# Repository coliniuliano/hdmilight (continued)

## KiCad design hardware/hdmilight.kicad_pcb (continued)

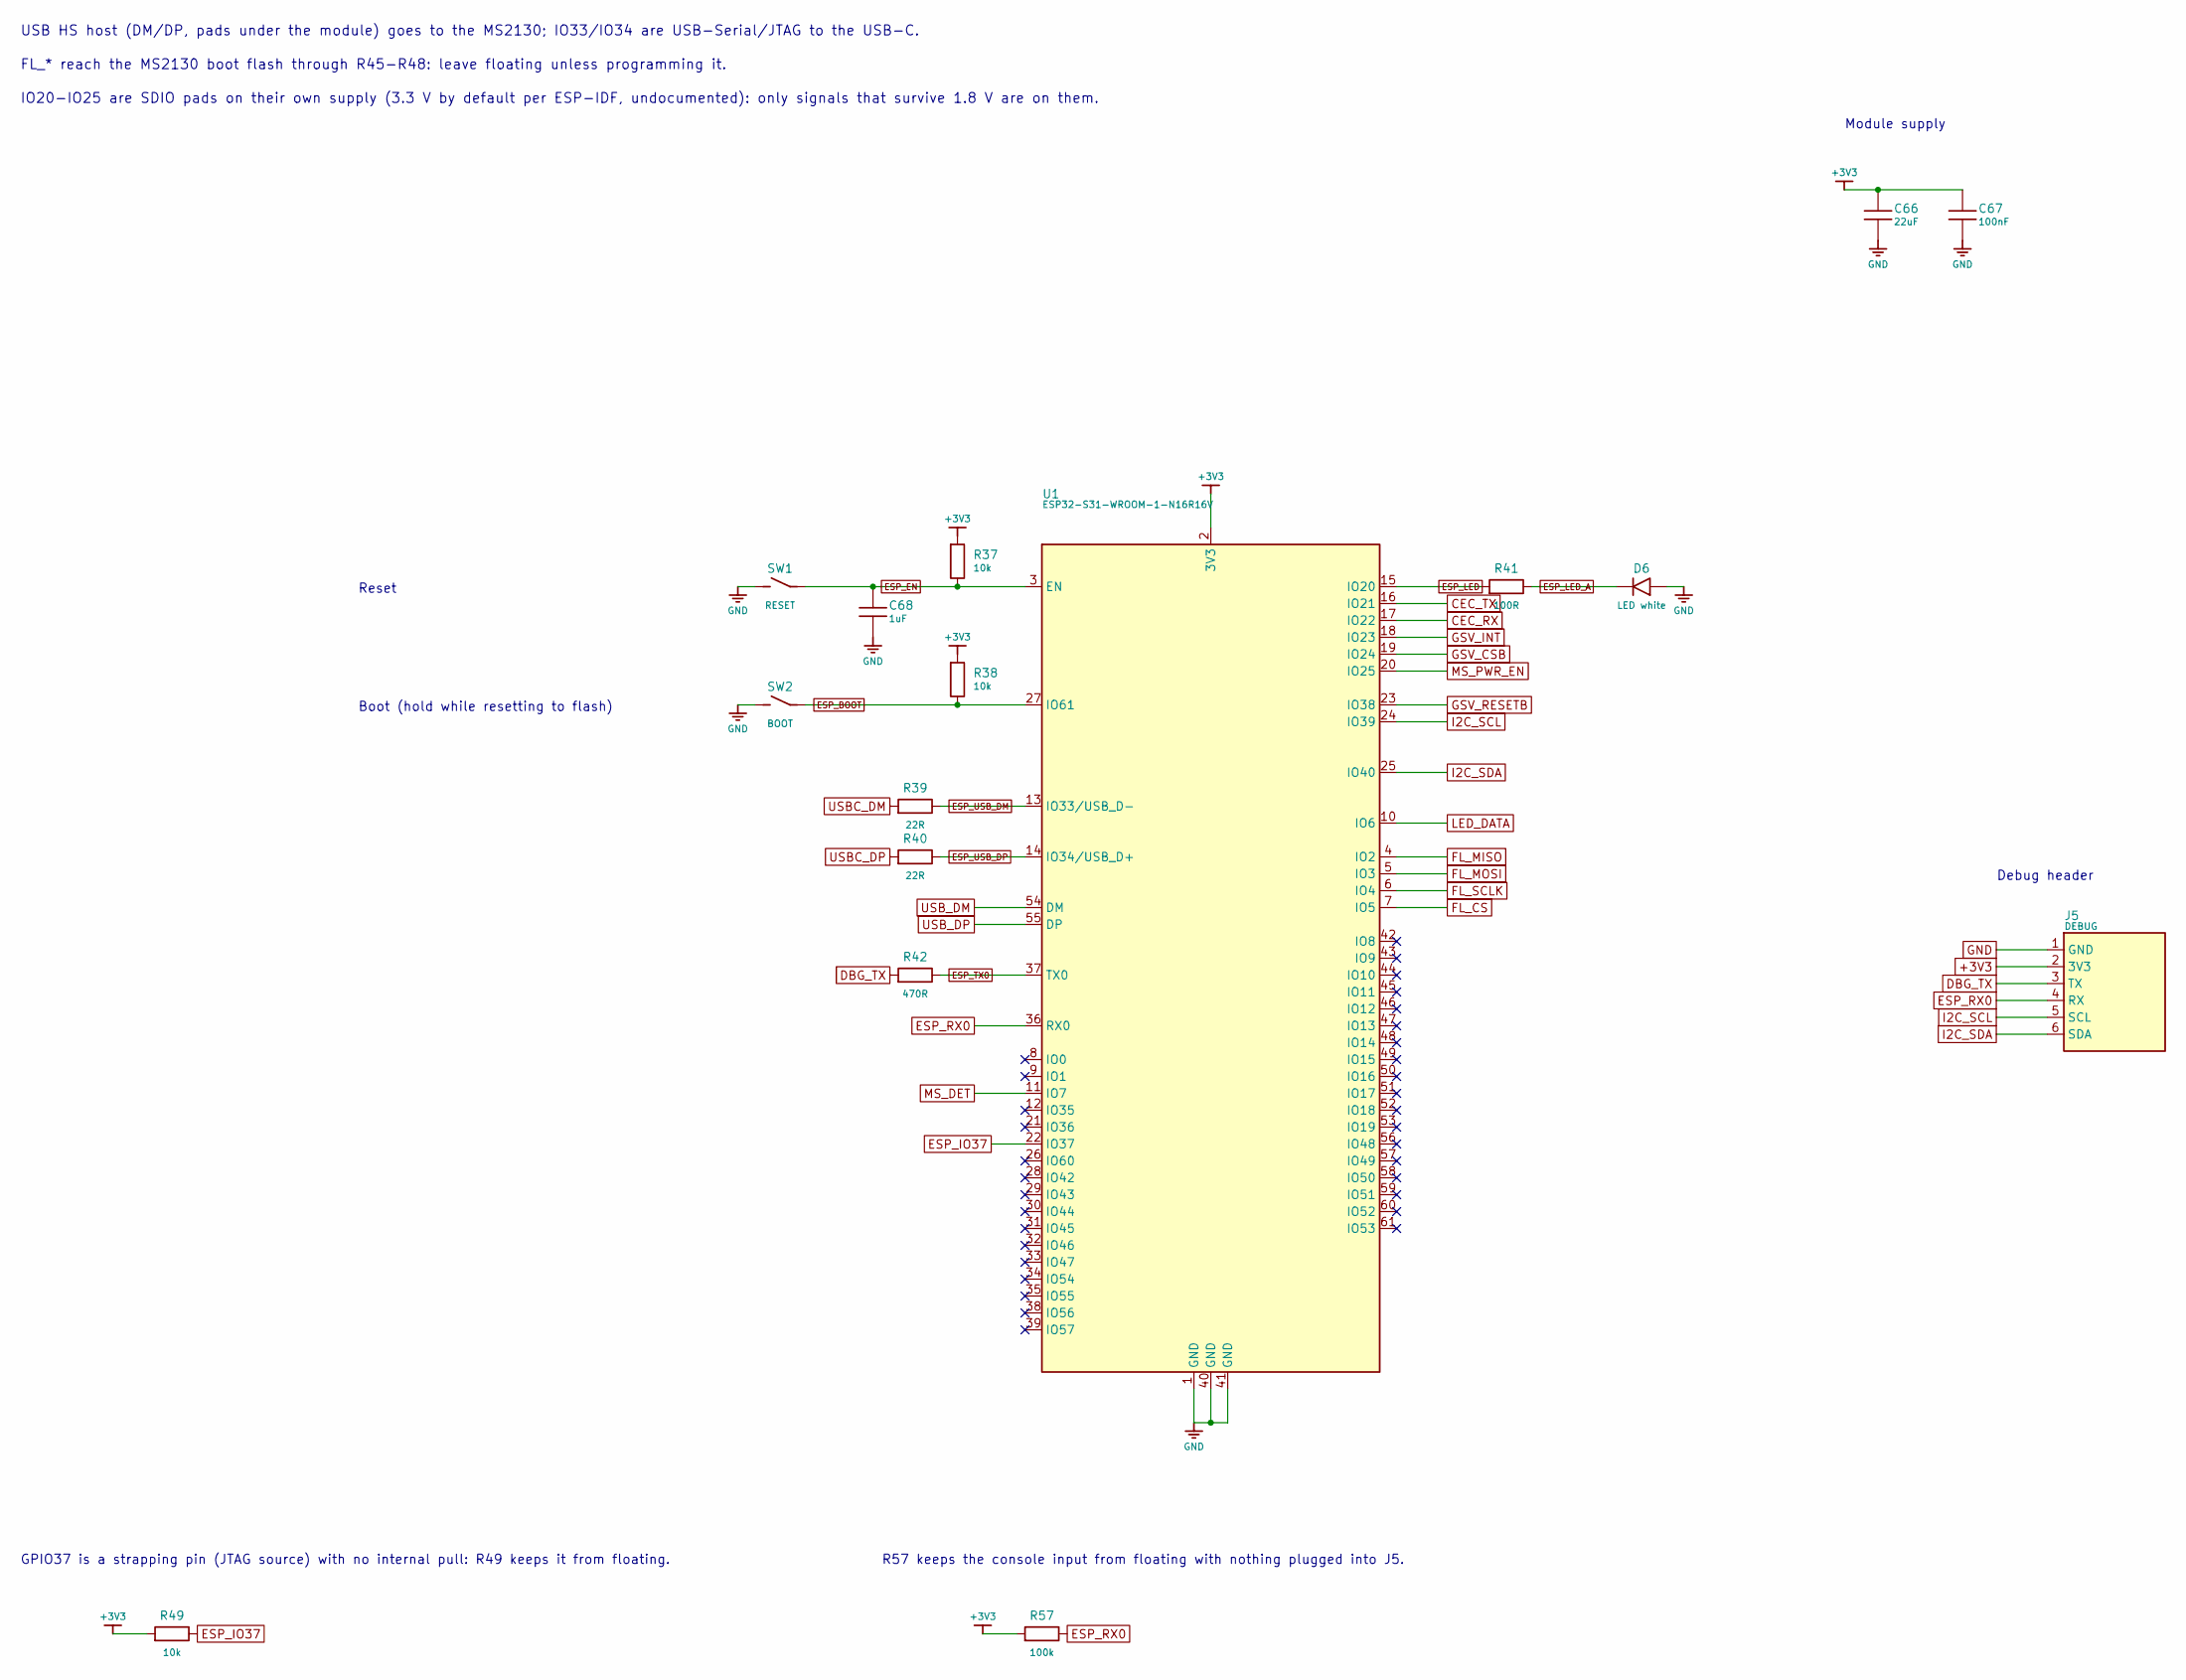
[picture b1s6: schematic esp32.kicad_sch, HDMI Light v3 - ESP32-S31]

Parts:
C66: 22uF; C_0805_2012Metric; LCSC C45783
C67: 100nF; C_0603_1608Metric; LCSC C14663
C68: 1uF; C_0603_1608Metric; LCSC C15849
D6: LED white; LED_0603_1608Metric; LCSC C2290
J5: DEBUG; PinHeader_1x06_P2.54mm_Vertical; LCSC C37208
R37, R38, R49: 10k; R_0603_1608Metric; LCSC C25804
R39, R40: 22R; R_0603_1608Metric; LCSC C23345
R41: 100R; R_0603_1608Metric; LCSC C22775
R42: 470R; R_0603_1608Metric; LCSC C23179
R57: 100k; R_0603_1608Metric; LCSC C25803
SW1: RESET; SW_SPST_B3U-1000P; MPN B3U-1000P; LCSC C231329
SW2: BOOT; SW_SPST_B3U-1000P; MPN B3U-1000P; LCSC C231329
U1: ESP32-S31-WROOM-1-N16R16V; ESP32-S31-WROOM-1; MPN ESP32-S31-WROOM-1-N16R16V

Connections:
+3V3: C66.1, C67.1, J5.2 (3V3), R37.1, R38.1, R49.1, R57.2, U1.2 (3V3); also elsewhere on the board
CEC_RX: U1.17 (IO22); also elsewhere on the board
CEC_TX: U1.16 (IO21); also elsewhere on the board
DBG_TX: J5.3 (TX), R42.2
ESP_BOOT: R38.2, SW2.1, U1.27 (IO61)
ESP_EN: C68.1, R37.2, SW1.1, U1.3 (EN)
ESP_IO37: R49.2, U1.22 (IO37)
ESP_LED: R41.1, U1.15 (IO20)
ESP_LED_A: D6.2, R41.2
ESP_RX0: J5.4 (RX), R57.1, U1.36 (RX0)
ESP_TX0: R42.1, U1.37 (TX0)
ESP_USB_DM: R39.2, U1.13 (IO33/USB_D-)
ESP_USB_DP: R40.2, U1.14 (IO34/USB_D+)
FL_CS: U1.7 (IO5); also elsewhere on the board
FL_MISO: U1.4 (IO2); also elsewhere on the board
FL_MOSI: U1.5 (IO3); also elsewhere on the board
FL_SCLK: U1.6 (IO4); also elsewhere on the board
GND: C66.2, C67.2, C68.2, D6.1, J5.1 (GND), SW1.2, SW2.2, U1.1 (GND), U1.40 (GND), U1.41 (GND); also elsewhere on the board
GSV_CSB: U1.19 (IO24); also elsewhere on the board
GSV_INT: U1.18 (IO23); also elsewhere on the board
GSV_RESETB: U1.23 (IO38); also elsewhere on the board
I2C_SCL: J5.5 (SCL), U1.24 (IO39); also elsewhere on the board
I2C_SDA: J5.6 (SDA), U1.25 (IO40); also elsewhere on the board
LED_DATA: U1.10 (IO6); also elsewhere on the board
MS_DET: U1.11 (IO7); also elsewhere on the board
MS_PWR_EN: U1.20 (IO25); also elsewhere on the board
USBC_DM: R39.1; also elsewhere on the board
USBC_DP: R40.1; also elsewhere on the board
USB_DM: U1.54 (DM); also elsewhere on the board
USB_DP: U1.55 (DP); also elsewhere on the board

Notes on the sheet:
Reset
Boot (hold while resetting to flash)
Module supply
GPIO37 is a strapping pin (JTAG source) with no internal pull: R49 keeps it from floating.
R57 keeps the console input from floating with nothing plugged into J5.
Debug header
USB HS host (DM/DP, pads under the module) goes to the MS2130; IO33/IO34 are USB-Serial/JTAG to the USB-C.
FL_* reach the MS2130 boot flash through R45-R48: leave floating unless programming it.
IO20-IO25 are SDIO pads on their own supply (3.3 V by default per ESP-IDF, undocumented): only signals that survive 1.8 V are on them.

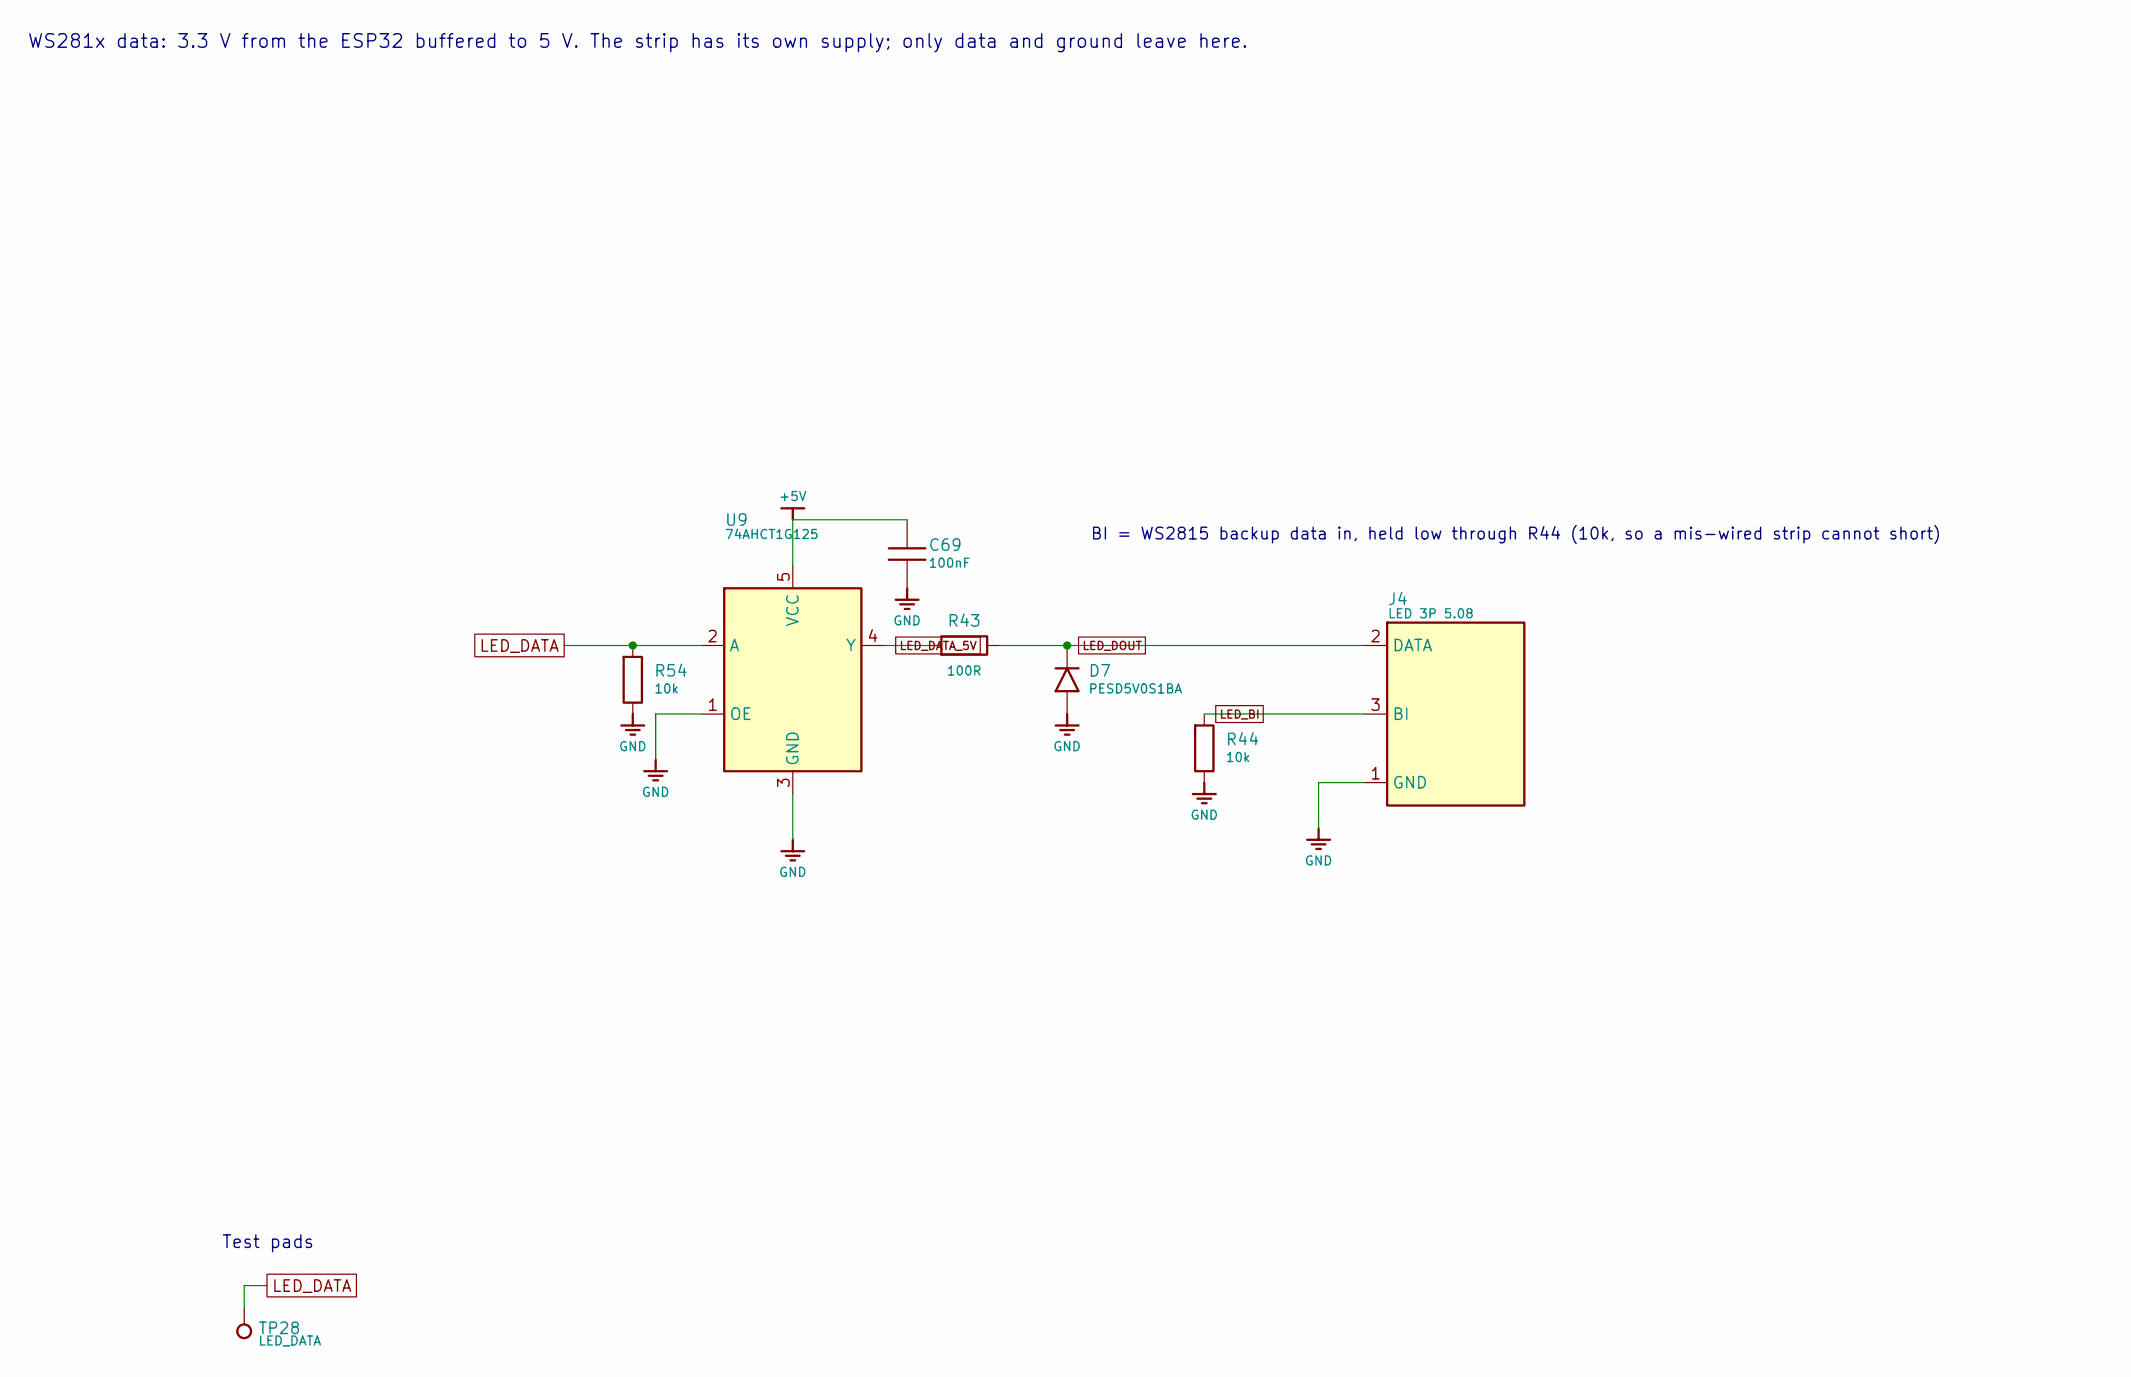
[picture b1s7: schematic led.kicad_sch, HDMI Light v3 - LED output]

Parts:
C69: 100nF; C_0603_1608Metric; LCSC C14663
D7: PESD5V0S1BA; D_SOD-323; MPN PESD5V0S1BA; LCSC C5261083
J4: LED 3P 5.08; PhoenixContact_MSTBA_2,5_3-G-5,08_1x03_P5.08mm_Horizontal; MPN MSTBA 2,5/3-G-5,08; LCSC C441205
R43: 100R; R_0603_1608Metric; LCSC C22775
R44, R54: 10k; R_0603_1608Metric; LCSC C25804
TP28: LED_DATA; TestPoint_Pad_D1.0mm
U9: 74AHCT1G125; SOT-23-5; MPN SN74AHCT1G125DBVR; LCSC C7484

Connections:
+5V: C69.1, U9.5 (VCC); also elsewhere on the board
GND: C69.2, D7.2, J4.1 (GND), R44.2, R54.2, U9.1 (OE), U9.3 (GND); also elsewhere on the board
LED_BI: J4.3 (BI), R44.1
LED_DATA: R54.1, TP28.1, U9.2 (A); also elsewhere on the board
LED_DATA_5V: R43.1, U9.4 (Y)
LED_DOUT: D7.1, J4.2 (DATA), R43.2

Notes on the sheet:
WS281x data: 3.3 V from the ESP32 buffered to 5 V. The strip has its own supply; only data and ground leave here.
BI = WS2815 backup data in, held low through R44 (10k, so a mis-wired strip cannot short)
Test pads

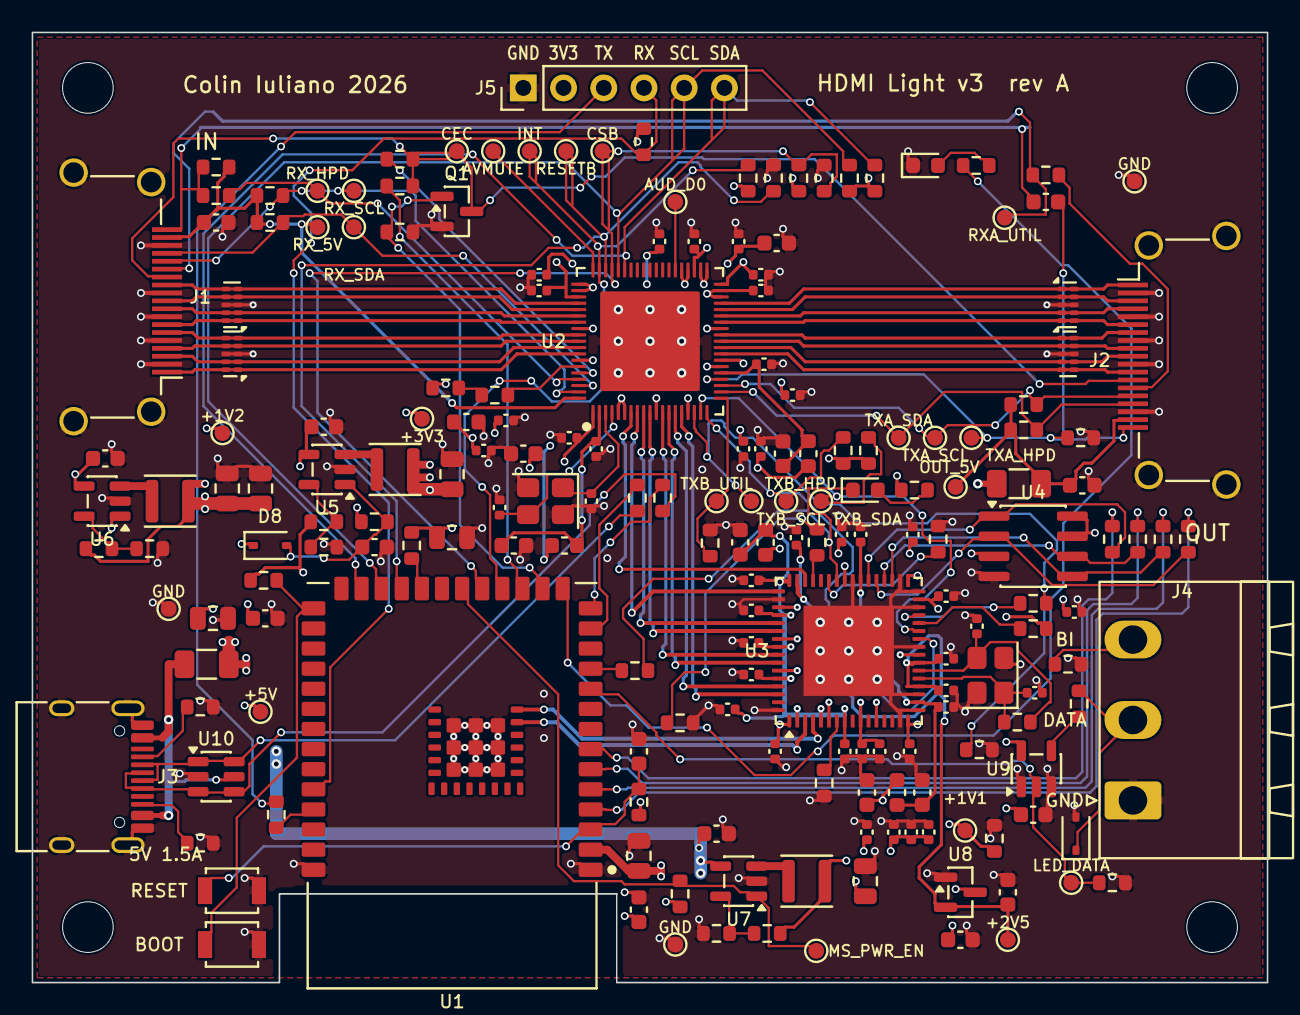
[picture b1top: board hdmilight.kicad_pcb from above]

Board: 4 copper layers, 78.0 x 60.0 mm, 198 parts (0 on the bottom side), 112 nets.

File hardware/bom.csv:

Qty,References,Value,Footprint,MPN,LCSC,Fit
7,C1 C4 C5 C7 C8 C11 C66,22uF,C_0805_2012Metric,,C45783,
38,C16 C17 C18 C19 C20 C21 C22 C23 C24 C25 C26 C27 C28 C32 C34 C38 C39 C40 C41 C42 C43 C45 C46 C47 C48 C49 C50 C51 C52 C53 C54 C55 C56 C57 C58 C60 C61 C65,100nF,C_0402_1005Metric,,C1525,
4,C2 C15 C67 C69,100nF,C_0603_1608Metric,,C14663,
9,C3 C6 C10 C29 C30 C31 C44 C59 C62,10uF,C_0603_1608Metric,,C19702,
2,C36 C37,15pF,C_0402_1005Metric,,C1548,
2,C63 C64,18pF,C_0402_1005Metric,,C1549,
1,C70,1uF,C_0603_1608Metric,,C15849,DO NOT FIT
7,C9 C12 C13 C14 C33 C35 C68,1uF,C_0603_1608Metric,,C15849,
4,D1 D2 D3 D4,RClamp0524P,USON-10_2.5x1.0mm_P0.5mm,RClamp0524PATCT,C40960,
1,D5,LED red,LED_0603_1608Metric,,C2286,
1,D6,LED white,LED_0603_1608Metric,,C2290,
1,D7,PESD5V0S1BA,D_SOD-323,PESD5V0S1BA,C5261083,
1,D8,1N4148WS,D_SOD-323,1N4148WS,C2128,
1,F1,1.5A PTC,Fuse_1206_3216Metric,BSMD1206-150-16V,C883133,
1,F2,0.5A PTC,Fuse_1206_3216Metric,JK-nSMD050-30,C720075,
4,FB1 FB2 FB3 FB4,120R@100MHz,L_0603_1608Metric,BLM18PG121SN1D,C14709,
2,J1 J2,HDMI-A,HDMI_A_Amphenol_10029449-x01xLF_Horizontal,10029449-111RLF,C427307,
1,J3,USB-C 16P,USB_C_Receptacle_HRO_TYPE-C-31-M-12,TYPE-C-31-M-12,C165948,
1,J4,LED 3P 5.08,"PhoenixContact_MSTBA_2,5_3-G-5,08_1x03_P5.08mm_Horizontal","MSTBA 2,5/3-G-5,08",C441205,
1,J5,DEBUG,PinHeader_1x06_P2.54mm_Vertical,,C37208,
3,L1 L2 L3,2.2uH,L_Changjiang_FNR3012S,SWPA3015S2R2MT,C43389,
1,Q1,2N7002,SOT-23,2N7002,C8545,
2,R1 R2,5.1k,R_0603_1608Metric,,C23186,
2,R11 R12,47k,R_0603_1608Metric,,C25819,
4,R13 R35 R36 R56,1k,R_0603_1608Metric,,C21190,
2,R14 R15,1.8k,R_0603_1608Metric,,C4177,
1,R17,0R,R_0603_1608Metric,,C21189,
2,R20 R28,1M,R_0603_1608Metric,,C22935,
3,R21 R29 R50,200R 1%,R_0603_1608Metric,,C8218,
4,R22 R23 R33 R34,4.7k,R_0603_1608Metric,,C23162,
1,R26,10k,R_0603_1608Metric,,C25804,DO NOT FIT
12,R3 R4 R8 R10 R24 R25 R27 R37 R38 R44 R49 R54,10k,R_0603_1608Metric,,C25804,
2,R30 R31,1.5k,R_0603_1608Metric,,C22843,
1,R32,0R,R_0603_1608Metric,,C21189,DO NOT FIT
2,R39 R40,22R,R_0603_1608Metric,,C23345,
3,R41 R43 R51,100R,R_0603_1608Metric,,C22775,
2,R42 R58,470R,R_0603_1608Metric,,C23179,
4,R45 R46 R47 R48,220R,R_0603_1608Metric,,C22962,
8,R5 R7 R16 R18 R19 R52 R53 R57,100k,R_0603_1608Metric,,C25803,
1,R55,1k,R_0603_1608Metric,,C21190,DO NOT FIT
1,R6,22k,R_0603_1608Metric,,C31850,
1,R9,12k,R_0603_1608Metric,,C22790,
1,SW1,RESET,SW_SPST_B3U-1000P,B3U-1000P,C231329,
1,SW2,BOOT,SW_SPST_B3U-1000P,B3U-1000P,C231329,
1,U1,ESP32-S31-WROOM-1-N16R16V,ESP32-S31-WROOM-1,ESP32-S31-WROOM-1-N16R16V,,
1,U10,USBLC6-2SC6,SOT-23-6,USBLC6-2SC6,C7519,
1,U2,GSV2001,QFN-76-1EP_9x9mm_P0.4mm_EP6.3x6.3mm,GSV2001,,
1,U3,MS2130,QFN-64-1EP_9x9mm_P0.5mm_EP5.7x5.7mm,MS2130,C5905137,
1,U4,W25Q80DVSNIG,SOIC-8_3.9x4.9mm_P1.27mm,W25Q80DVSNIG,C401655,
3,U6 U5 U7,SY8089AAAC,SOT-23-5,SY8089AAAC,C78988,
1,U8,XC6206P252MR,SOT-23,XC6206P252MR,C545580,
1,U9,74AHCT1G125,SOT-23-5,SN74AHCT1G125DBVR,C7484,
1,Y1,27MHz 12pF,Crystal_SMD_3225-4Pin_3.2x2.5mm,X322527MOB4SI,C70595,
1,Y2,24MHz 12pF,Crystal_SMD_3225-4Pin_3.2x2.5mm,X322524MOB4SI,C70590,
